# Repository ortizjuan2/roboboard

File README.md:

# roboboard
Eagle schematic for a differential drive robot

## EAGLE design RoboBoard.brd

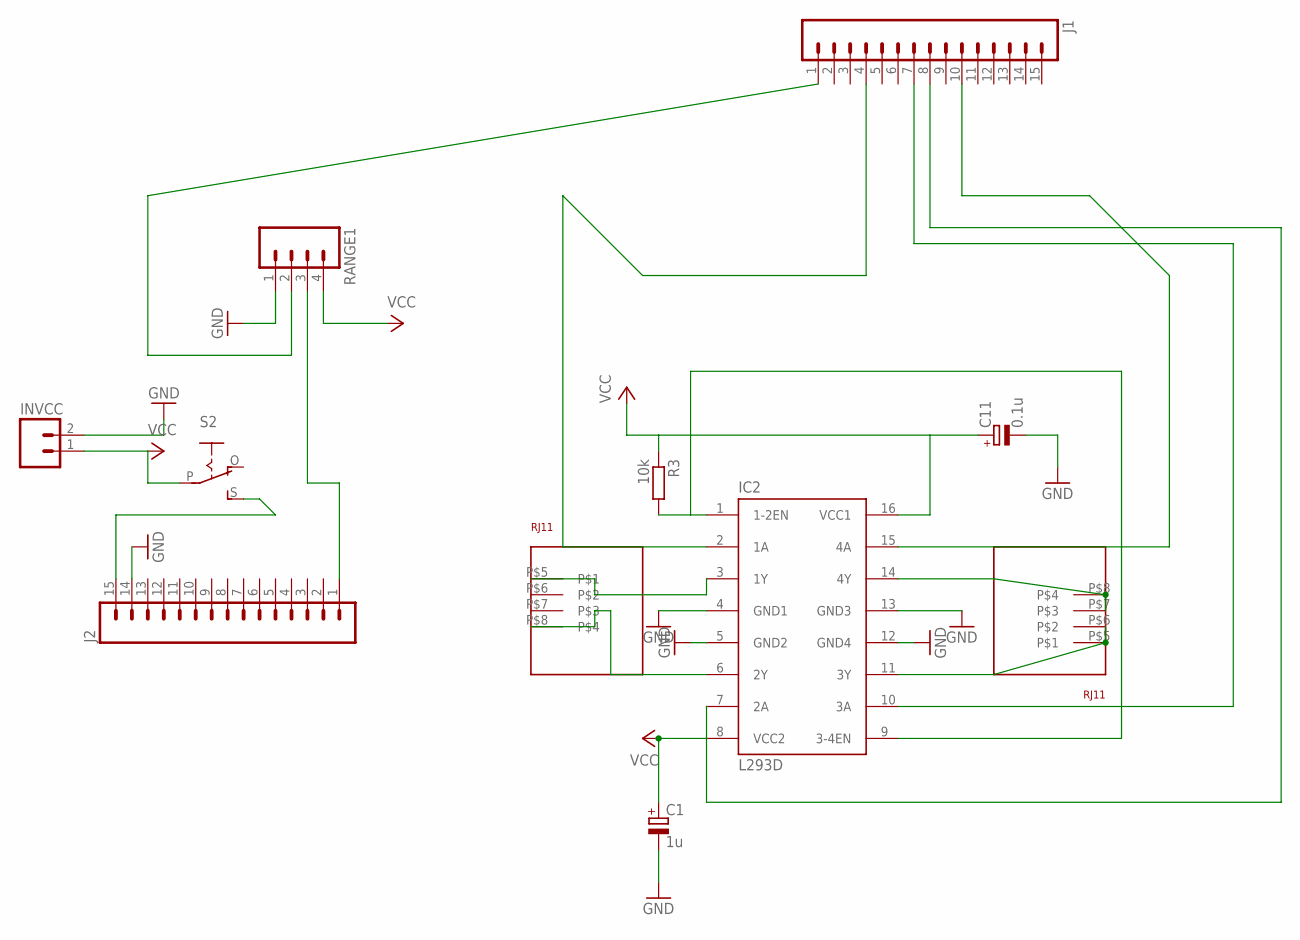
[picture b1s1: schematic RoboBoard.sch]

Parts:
C1: 1u; E1,8-4
C11: 0.1u; E1,8-4
IC2: L293D; DIL16
INVCC: M02LOCK_LONGPADS; 1X02_LOCK_LONGPADS
J1, J2: M15LOCK_LONGPADS; 1X15_LOCK_LONGPADS
R3: 10k; 0204/7
RANGE1: M04LONGPADS; 1X04_LONGPADS
RJ1, RJ2: RJ11; RJ11-4PIN
S2: EG1218S; EG1218

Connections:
GND: C1.-, C11.-, IC2.4 (GND1), IC2.5 (GND2), IC2.12 (GND4), IC2.13 (GND3), INVCC.2, J2.14, RANGE1.1
unnamed: IC2.3 (1Y), RJ1.P$5
unnamed: IC2.6 (2Y), RJ1.P$8
unnamed: IC2.11 (3Y), RJ2.P$5, RJ2.P$6
unnamed: IC2.14 (4Y), RJ2.P$7, RJ2.P$8
unnamed: IC2.15 (4A), J1.10
unnamed: J2.1, RANGE1.3
unnamed: IC2.10 (3A), J1.7
unnamed: IC2.1 (1-2EN), IC2.9 (3-4EN), R3.2
unnamed: IC2.7 (2A), J1.8
unnamed: IC2.2 (1A), J1.4
unnamed: J1.1, RANGE1.2
unnamed: J2.15, S2.S
VCC: C1.+, C11.+, IC2.8 (VCC2), IC2.16 (VCC1), INVCC.1, R3.1, RANGE1.4, S2.P

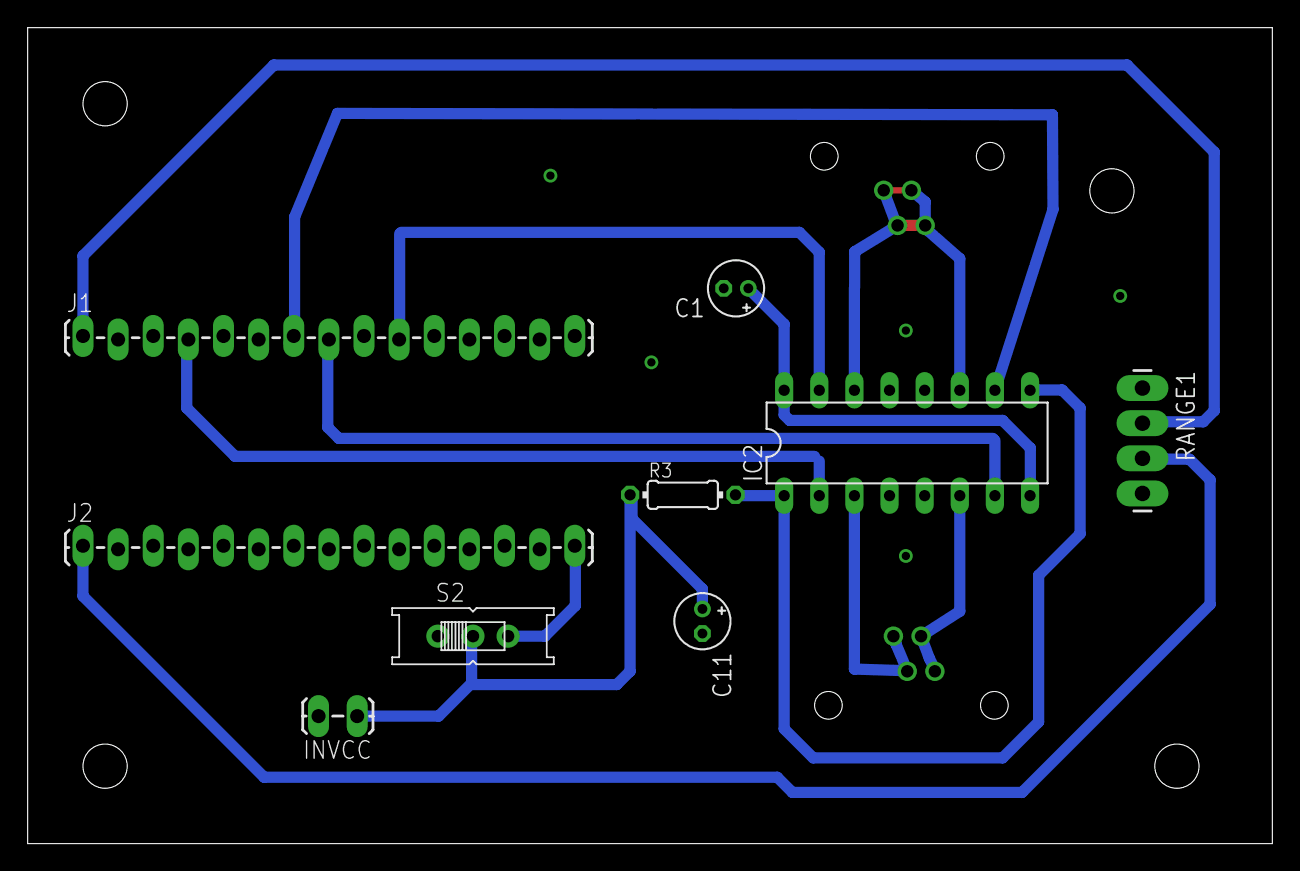
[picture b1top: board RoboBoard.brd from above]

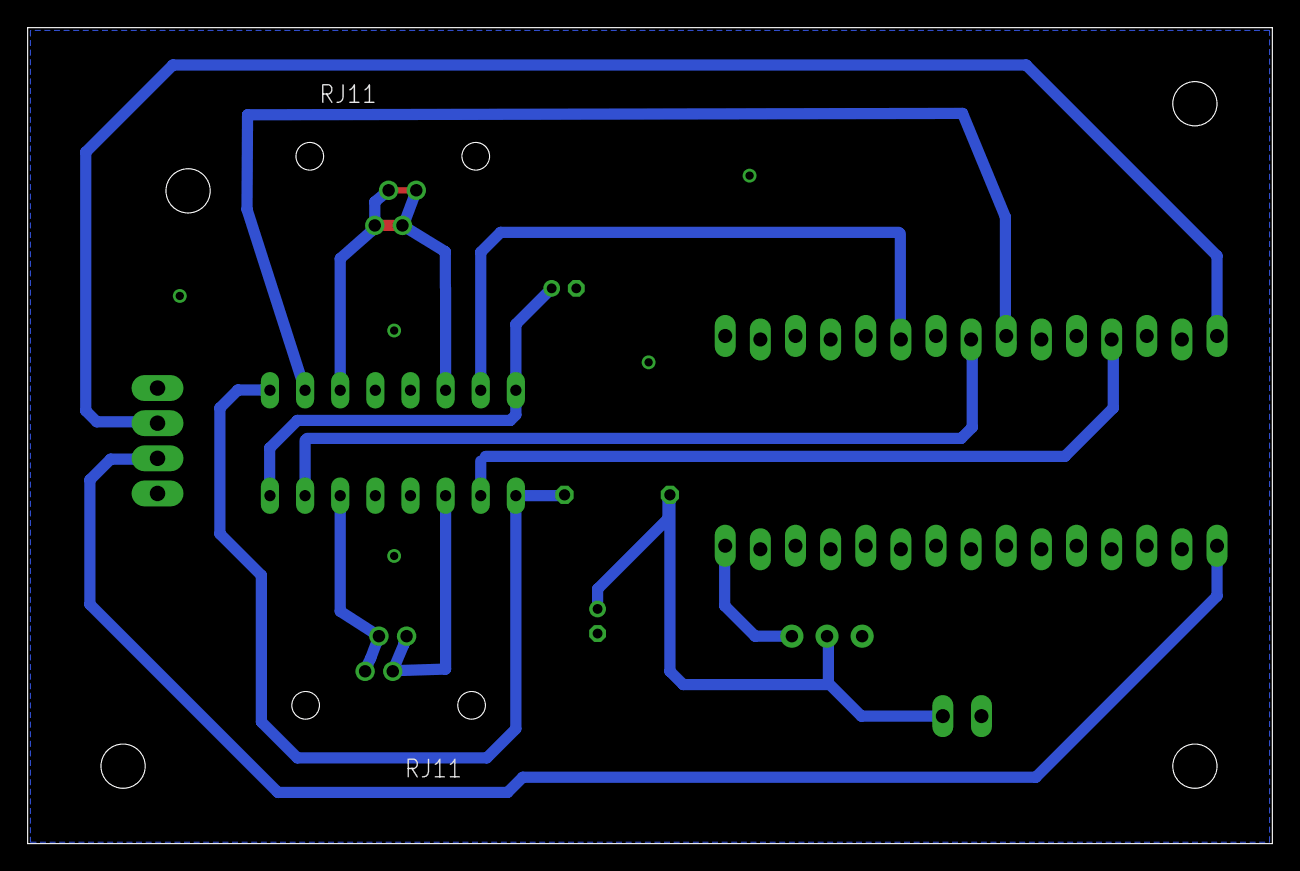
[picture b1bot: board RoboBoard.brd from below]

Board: 2 copper layers, 90.0 x 59.0 mm, 11 parts (2 on the bottom side), 14 nets.

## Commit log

2017-04-11 feat: Initial version
    Initial version
2017-04-11 Create README.md
    Create readme file
2017-04-20 feat: Adding sonar and ld293 classes
    Adding the classes to control the radar and ld293 motor driver
2017-04-21 fix: Fixing motor rotations
    Fixin motor rotations to allow left and rights turns.
2017-04-24 fix: Fixing board layout
    Fixing the board layout
2017-06-14 refactory: Separate ld293 routines
    Separate ld293 routines from main file
2017-06-14 feat: Adding bluetooth
    Adding bluetooth to command robot
2017-06-14 fix: Fixing movements
    Fixing movements in ld293 driver
2017-06-16 feat: Adding down movement
    Adding reverse movement
2017-06-17 feat: Adding bluetooth commands
    Adding bluetooth commands to drive robot
2017-06-17 feat: Adding Android app
    Adding Android app to control robot movement
2017-06-17 refactory: Changing name commands
    Changing the name of commands in home page
2017-07-23 fix: Fixing baud rate Fixing baud rate to 9600 to improve communication with phone

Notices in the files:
parts and their libraries:
SparkFun-Connectors: Licensing: Creative Commons ShareAlike 4.0 International - https://creativecommons.org/licenses/by-sa/4.0
